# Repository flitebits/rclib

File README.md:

*RCLib*

This is a basic example of bringing up the ATMega 4808/4809 and
enabling the most common hardware. I wrote this so I could use it to
control various features in RC aircraft (telemetry and lights mostly).

I also have some small board designs for the 4808/4809 that I may
include as well.

It has support for:
  * SBus protocol (channel information from radio)
  * S.Port Protocol (only for volts/amps reporting)
  * DSHOT 600 (bit bang) to set motor speed and get telemetry from ESC
  * Analog to Digital conversion (to read battery volts/amps)
  * PWM for controlling 'dumb' leds
  * APA102 (via SPI) & WS2812 (via bit bang)
  * Serial used by several protocols above as well as for debugging
  * Some simple RGB functions for LED control
  * Very minimal debugging log/print support
  * RTC clock

Licensed under the Apache 2.0 license (see the file LICENSE-2.0 for
details).  Please let me know if you decide to use it.

Flite Bits
flitebits@gmail.com

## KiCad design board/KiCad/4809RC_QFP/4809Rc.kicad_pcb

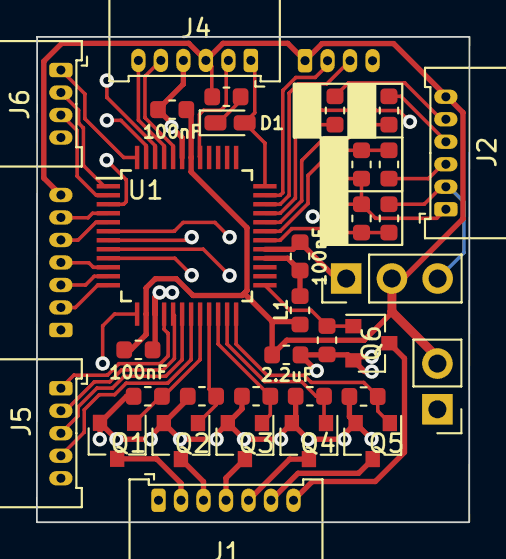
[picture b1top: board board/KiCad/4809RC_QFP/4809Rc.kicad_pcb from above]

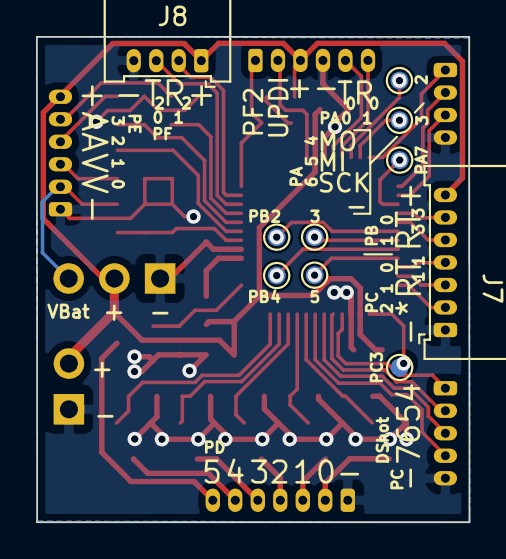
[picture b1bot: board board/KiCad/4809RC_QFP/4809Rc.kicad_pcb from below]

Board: 2 copper layers, 24.0 x 27.0 mm, 47 parts (10 on the bottom side), 50 nets.

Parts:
2.2uF1: 2.2uF; C_0603_1608Metric
100nF1, 100nF2, 100nF3: 100nF; C_0603_1608Metric
C1, C2, C3, C4: 1uF; C_0603_1608Metric
D1: LED; LED_0603_1608Metric_Castellated
J1: Conn_01x09_Male; Molex_PicoBlade_53048-0710_1x07_P1.25mm_Horizontal
J2, J4: Conn_01x06_Male; Molex_PicoBlade_53048-0610_1x06_P1.25mm_Horizontal
J3: Conn_01x03_Female; PinHeader_1x03_P2.54mm_Vertical
J5: Conn_01x05_Male; Molex_PicoBlade_53048-0510_1x05_P1.25mm_Horizontal
J6, J8: Conn_01x04_Male; Molex_PicoBlade_53048-0410_1x04_P1.25mm_Horizontal
J7: Conn_01x07_Male; Molex_PicoBlade_53048-0710_1x07_P1.25mm_Horizontal
J9: Conn_01x02_Male; PinHeader_1x02_P2.54mm_Vertical
L1: L_Core_Ferrite; L_0603_1608Metric
PC3: TestPoint; TestPoint_Pad_D1.0mm
Q1, Q2, Q3, Q4, Q5, Q6: Q_NMOS_GSD; SOT-23
R1, R2, R3, R4, R7, R8: 10K; R_0603_1608Metric
R5, R10: 100K; R_0603_1608Metric
R6, R11: 33K; R_0603_1608Metric
R9, R12, R13: 1K; R_0603_1608Metric
TP1, TP2, TP3, TP4, TP5, TP6, TP7: TestPoint; TestPoint_Pad_D1.0mm
U1: ATmega4809-M; TQFP-48_7x7mm_P0.5mm

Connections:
+5V: 2.2uF1.1, 100nF1.1, 100nF2.1, J2.6, J3.2, J4.3, J7.7, J8.1, J9.2, L1.1, R13.2, U1.14, U1.42
GND: 2.2uF1.2, 100nF1.2, 100nF2.2, 100nF3.2, C1.2, C2.2, C3.2, C4.2, J1.1, J2.1, J3.1, J4.4, J5.5, J6.4, J7.1, J8.4, J9.1, Q1.2, Q2.2, Q3.2, Q4.2, Q5.2, Q6.2, R1.2, R2.2, R3.2, R4.2, R6.2, R7.2, R8.2, R11.2, U1.15, U1.29, U1.43
unnamed: 100nF3.1, L1.2, U1.28
unnamed: C1.1, R5.2, R6.1, U1.31
unnamed: C2.1, R9.2, U1.33
unnamed: C3.1, R10.2, R11.1, U1.30
unnamed: C4.1, R12.2, U1.32
unnamed: D1.1, R13.1
unnamed: D1.2, J4.1, U1.36
unnamed: J1.2, Q1.3
unnamed: J1.3, Q2.3
unnamed: J1.4, Q3.3
unnamed: J1.5, Q4.3
unnamed: J1.6, Q5.3
unnamed: J1.7, Q6.3
unnamed: J2.2, J3.3, R10.1
unnamed: J2.3, R5.1
unnamed: J2.4, R12.1
unnamed: J2.5, R9.1
unnamed: J4.2, U1.41
unnamed: J4.5, U1.44
unnamed: J4.6, U1.45
unnamed: J5.1, U1.16
unnamed: J5.2, U1.17
unnamed: J5.3, U1.18
unnamed: J5.4, U1.19
unnamed: J6.1, U1.48
unnamed: J6.2, U1.1
unnamed: J6.3, U1.2
unnamed: J7.2, U1.12
unnamed: J7.3, U1.11
unnamed: J7.4, U1.10
unnamed: J7.5, U1.5
unnamed: J7.6, U1.4
unnamed: J8.2, U1.35
unnamed: J8.3, U1.34
unnamed: Q1.1, R1.1, U1.20
unnamed: Q2.1, R4.1, U1.21
unnamed: Q3.1, R7.1, U1.22
unnamed: Q4.1, R2.1, U1.23
unnamed: Q5.1, R3.1, U1.24
unnamed: Q6.1, R8.1, U1.25
unnamed: TP1.1, U1.46
unnamed: TP2.1, U1.47
unnamed: TP3.1, U1.6
unnamed: TP4.1, U1.7
unnamed: TP5.1, U1.3
unnamed: TP6.1, U1.8
unnamed: TP7.1, U1.9
unnamed: PC3.1, U1.13

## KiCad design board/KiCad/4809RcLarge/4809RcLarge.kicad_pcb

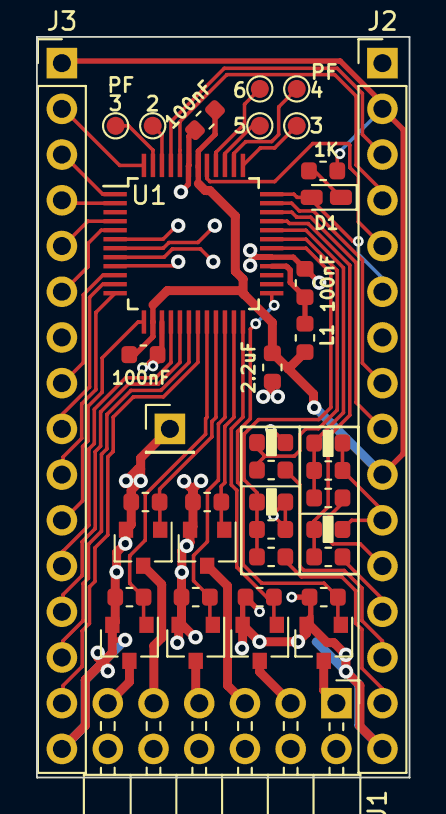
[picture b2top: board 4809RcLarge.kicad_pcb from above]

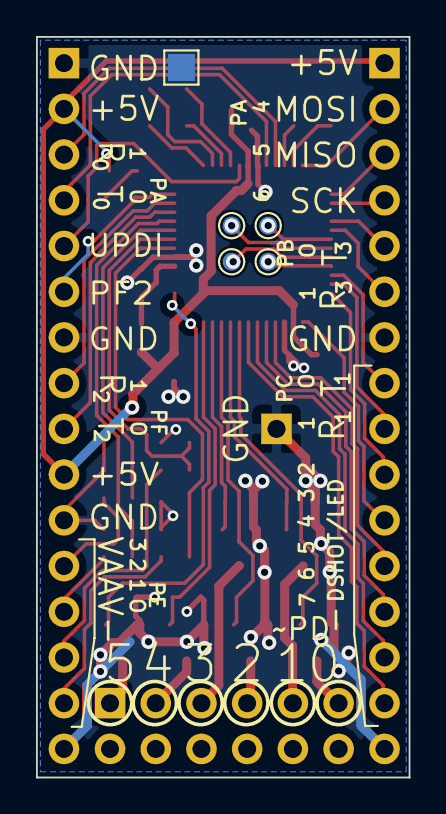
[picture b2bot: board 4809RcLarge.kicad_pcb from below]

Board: 2 copper layers, 20.7 x 41.1 mm, 45 parts (5 on the bottom side), 54 nets.

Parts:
2.2uF, 100nF#2, 100nF#3: 100nF; C_0603_1608Metric
100nF: 2.2uF; C_0603_1608Metric
C1, C2, C3, C4: 1uF; C_0603_1608Metric
D1: LED; LED_0603_1608Metric_Castellated
J1: `; PinHeader_2x06_P2.54mm_Horizontal
J2: Conn_01x06_Male; PinHeader_1x16_P2.54mm_Vertical
J3: Conn_01x16_Male; PinHeader_1x16_P2.54mm_Vertical
J4: Conn_01x01_Male; PinHeader_1x01_P2.54mm_Vertical
L1: L_Core_Ferrite; L_0603_1608Metric
Q1, Q2, Q3, Q4, Q5, Q6: Q_NMOS_GSD; SOT-23
R1, R2, R3, R4, R7, R8: 10K; R_0603_1608Metric
R5, R6: 100K; R_0603_1608Metric
R9, R12, R13: 1K; R_0603_1608Metric
R10, R11: 33K; R_0603_1608Metric
TP1: TestPoint; TestPoint_Pad_1.5x1.5mm
TP2, TP3, TP4, TP5, TP6, TP7, TP8, TP9, TP10, TP11: TestPoint; TestPoint_Pad_D1.0mm
U1: ATmega4809-A; TQFP-48_7x7mm_P0.5mm

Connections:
+5V: 2.2uF.1, 100nF.1, 100nF#3.1, J2.2, J2.10, J3.1, L1.1, R13.2, U1.14, U1.42
GND: 2.2uF.2, 100nF.2, 100nF#2.2, 100nF#3.2, C1.2, C2.2, C3.2, C4.2, J2.1, J2.7, J2.11, J2.16, J3.7, J3.16, J4.1, Q1.2, Q2.2, Q3.2, Q4.2, Q5.2, Q6.2, R1.2, R2.2, R3.2, R4.2, R6.2, R7.2, R8.2, R11.2, TP1.1, U1.15, U1.29, U1.43
unnamed: C1.1, R5.2, R6.1, U1.32
unnamed: C2.1, R9.2, U1.33
unnamed: C3.1, R10.2, R11.1, U1.30
unnamed: C4.1, R12.2, U1.31
unnamed: 100nF#2.1, L1.2, U1.28
unnamed: D1.1, R13.1
unnamed: D1.2, J2.6, U1.36
unnamed: J1.1, Q6.3
unnamed: J1.3, Q3.3
unnamed: J1.5, Q2.3
unnamed: J1.7, Q5.3
unnamed: J1.9, Q4.3
unnamed: J1.11, Q1.3
unnamed: J2.3, U1.45
unnamed: J2.4, U1.44
unnamed: J2.5, U1.41
unnamed: J2.8, U1.35
unnamed: J2.9, U1.34
unnamed: J2.12, R5.1
unnamed: J2.13, R9.1
unnamed: J2.14, R12.1
unnamed: J2.15, R10.1
unnamed: J3.2, U1.48
unnamed: J3.3, U1.1
unnamed: J3.4, U1.2
unnamed: J3.5, U1.4
unnamed: J3.6, U1.5
unnamed: J3.8, U1.10
unnamed: J3.9, U1.11
unnamed: J3.10, U1.12
unnamed: J3.11, U1.13
unnamed: J3.12, U1.16
unnamed: J3.13, U1.17
unnamed: J3.14, U1.18
unnamed: J3.15, U1.19
unnamed: Q1.1, R1.1, U1.20
unnamed: Q2.1, R2.1, U1.23
unnamed: Q3.1, R3.1, U1.24
unnamed: Q4.1, R4.1, U1.21
unnamed: Q5.1, R7.1, U1.22
unnamed: Q6.1, R8.1, U1.25
unnamed: TP2.1, U1.7
unnamed: TP3.1, U1.8
unnamed: TP4.1, U1.9
unnamed: TP5.1, U1.6
unnamed: TP6.1, U1.37
unnamed: TP7.1, U1.38
unnamed: TP8.1, U1.39
unnamed: TP9.1, U1.40
unnamed: TP10.1, U1.46
unnamed: TP11.1, U1.47
VCC: J1.2, J1.4, J1.6, J1.8, J1.10, J1.12

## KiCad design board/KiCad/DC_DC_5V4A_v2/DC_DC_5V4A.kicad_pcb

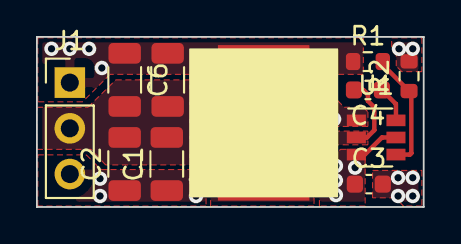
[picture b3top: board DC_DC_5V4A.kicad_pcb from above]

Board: 2 copper layers, 21.5 x 9.4 mm, 11 parts (0 on the bottom side), 6 nets.

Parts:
C1, C2: 10uF; C_1206_3216Metric
C3, C4: 100nF; C_0603_1608Metric
C5, C6: 22uF; C_1206_3216Metric
J1: Conn_01x02; PinHeader_1x03_P2.54mm_Vertical
L1: 3.3uH, 17.7.mOhm, 9.2A; L_Vishay_IHLP-3232
R1: 54.9kOhm; R_0603_1608Metric
R2: 10kOhm; R_0603_1608Metric
U1: TPS565208; SOT-23-6

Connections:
+5V: C5.1, C6.1, J1.1, L1.2, R1.1
+BATT: C1.1, C2.1, C3.1, J1.3, U1.3, U1.5
GND: C1.2, C2.2, C3.2, C5.2, C6.2, J1.2, R2.2, U1.1
unnamed: C4.1, U1.6
unnamed: C4.2, L1.1, U1.2
unnamed: R1.2, R2.1, U1.4

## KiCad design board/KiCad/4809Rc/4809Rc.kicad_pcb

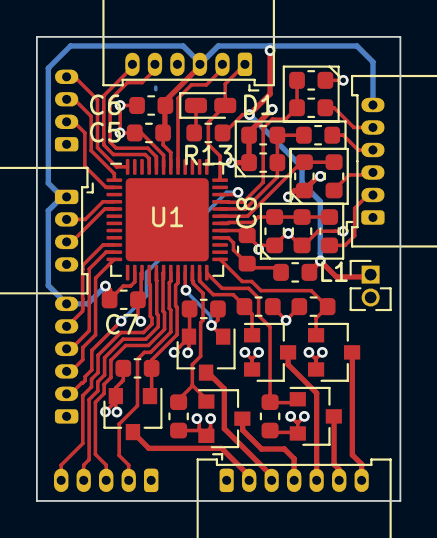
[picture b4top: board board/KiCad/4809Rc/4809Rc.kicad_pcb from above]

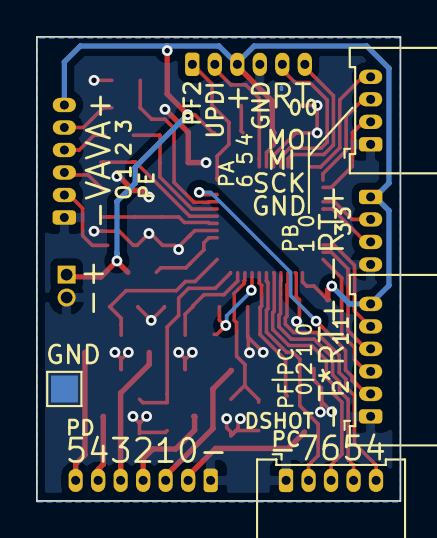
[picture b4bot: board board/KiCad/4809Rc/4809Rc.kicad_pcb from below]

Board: 2 copper layers, 20.2 x 25.8 mm, 39 parts (4 on the bottom side), 41 nets.

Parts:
C1, C2, C3, C4: 1uF; C_0603_1608Metric
C5, C6, C8: 100nF; C_0603_1608Metric
C7: 2.2uF; C_0603_1608Metric
D1: LED; LED_0603_1608Metric_Castellated
GND: TestPoint; TestPoint_Pad_1.5x1.5mm
J1: `; Molex_PicoBlade_53048-0710_1x07_P1.25mm_Horizontal
J2, J4: Conn_01x06_Male; Molex_PicoBlade_53048-0610_1x06_P1.25mm_Horizontal
J3: Conn_01x02; PinHeader_1x02_P1.27mm_Vertical
J5: Conn_01x05_Male; Molex_PicoBlade_53048-0510_1x05_P1.25mm_Horizontal
J6, J8: Conn_01x04_Male; Molex_PicoBlade_53048-0410_1x04_P1.25mm_Horizontal
J7: Conn_01x05_Male; Molex_PicoBlade_53048-0610_1x06_P1.25mm_Horizontal
L1: L_Core_Ferrite; L_0603_1608Metric
Q1, Q2, Q3, Q4, Q5, Q6: Q_NMOS_GSD; SOT-23
R1, R2, R3, R4, R7, R8: 10K; R_0603_1608Metric
R5, R6: 100K; R_0603_1608Metric
R9, R12, R13: 1K; R_0603_1608Metric
R10, R11: 33K; R_0603_1608Metric
U1: ATmega4809-M; UQFN-48-1EP_6x6mm_P0.4mm_EP4.62x4.62mm

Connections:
+5V: C5.1, C6.1, C7.1, J2.6, J3.1, J4.3, J7.6, J8.1, L1.1, R13.2, U1.14, U1.42
GND: C1.2, C2.2, C3.2, C4.2, C5.2, C6.2, C7.2, C8.2, GND.1, J1.1, J2.1, J3.2, J4.4, J5.1, J6.1, J7.1, J8.4, Q1.2, Q2.2, Q3.2, Q4.2, Q5.2, Q6.2, R1.2, R2.2, R3.2, R4.2, R6.2, R7.2, R8.2, R11.2, U1.15, U1.29, U1.43
unnamed: C1.1, R5.2, R6.1, U1.32
unnamed: C2.1, R9.2, U1.33
unnamed: C3.1, R10.2, R11.1, U1.30
unnamed: C4.1, R12.2, U1.31
unnamed: C8.1, L1.2, U1.28
unnamed: D1.1, R13.1
unnamed: D1.2, J4.1, U1.36
unnamed: J1.2, Q1.3
unnamed: J1.3, Q4.3
unnamed: J1.4, Q5.3
unnamed: J1.5, Q2.3
unnamed: J1.6, Q3.3
unnamed: J1.7, Q6.3
unnamed: J2.2, R10.1
unnamed: J2.3, R12.1
unnamed: J2.4, R5.1
unnamed: J2.5, R9.1
unnamed: J4.2, U1.41
unnamed: J4.5, U1.44
unnamed: J4.6, U1.45
unnamed: J5.2, U1.19
unnamed: J5.3, U1.18
unnamed: J5.4, U1.17
unnamed: J5.5, U1.16
unnamed: J6.2, U1.2
unnamed: J6.3, U1.1
unnamed: J6.4, U1.48
unnamed: J7.2, U1.34
unnamed: J7.3, U1.12
unnamed: J7.4, U1.11
unnamed: J7.5, U1.10
unnamed: J8.2, U1.4
unnamed: J8.3, U1.5
unnamed: Q1.1, R1.1, U1.20
unnamed: Q2.1, R2.1, U1.23
unnamed: Q3.1, R3.1, U1.24
unnamed: Q4.1, R4.1, U1.21
unnamed: Q5.1, R7.1, U1.22
unnamed: Q6.1, R8.1, U1.25

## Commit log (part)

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2019-10-03 Initial import to GIT.
2019-10-03 1) Added simple random function. 2) Added Led Fade functions that fade an array of pixels. 2) Added project for FTSportster plane leds.
2019-10-04 Fix compile errors in FTSportster/main.cpp Renamed Rand.cc to Rand.cpp
2019-10-19 1) Split pullup enable from one_wire config (I had trouble with older FrSky receivers doing s.Port with pullup). 2) Added 'App' class to Dbg for user code. 3) Fixed Dbg for Release builds. 4) Switch 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
2019-10-28 1) Added the ability to specify the voltage reference for ADC. 2) Fixed the RGB class order to WS2812, and had the APA102 code pull bytes out in the right order. 3) Added a P38 project that just repo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
2019-11-08 A small amount of cleanup and work on FT Sportster lights. Still need to integrate all the modes.
    Started a test project to try and get ESC Telemetry from a KISS enabled esc.
    So far no luck, I've checked timings for DSHOT 300 with an oscilliscope and they seem good. I kind of suspect I need to do something to prep the ESC. Anyway still a work in progress.
2019-11-11 1) Added a buffered serial option. This uses rx interrupt to read into a rolling buffer (32 bytes). SBus is now using this because driving WS2812 lights takes too much time. 2) Finished first cut of 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
2019-11-15 1) Add more info around interrupt driven Serial reads. It now tracks errors and the fine grained time of the read for time sensitive serial protocols. 2) Migrated SBus protocol to the new Serial inte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
2019-11-16 Added SK6812/WS2812 bitbang implementation. Switched FT Sportster to using that.
2019-12-19 1) Improved Dbg module to have _IF variants. 2) Enhanced Pins.h to make it more useful to work with identified pins. 3) Added needed Atomic block to Serial class. 4) Tweaks to bit bang WS2812 support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
2019-12-20 DShot class is working, and Test code can control motor and get Telemetry.
2020-01-05 1) DShot Implemetation improved a) Uses Asm function for bit banging (better timing) b) Has an ISR based version so you can take time doing other things and still have good timing. 2) Serial now uses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
2020-01-05 Added Apache License to project. Removed some not so interesting code (mostly from me playing around).
2020-02-05 1) Added new project 'Comet'. 2) Added WRGB Gradient lookup functions. 3) Added the ability to mix new random value into Rand seed. 4) Fixed DShot so it will compile in OPT mode (when debug prints ar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
2020-08-17 1) Retuned WS2812 bitbang for PDIV of 1. 2) Created a simple led test project.
2020-10-03 1) First cut of LED program for SkyBoy plane 2) Added Max operator for blending pixels.
2020-11-28 Lots of updates for DSHot related stuff. 1) Split Kiss telemetry out, for fixed wing where there is only one or two ESCs you can configure them with auto telemetry and connect them to different seria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
2020-11-29 1) Added ASM versions of bitbang methods, mostly to avoid compiler changes affecting timing. 2) Fixed argument order for memset (duh!) 3) Updated WingTelemetry for new KissTelemtry interface. 4) Fixe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
2020-12-02 1) Small tweak to KissTelemetry so it resets idx after a successful parse. 2) Fix telemetry requesting in Test/main.cpp 3) cleanup in WingTelem/main.cpp
2021-01-03 1) Added KiCad files for various boards and related items. This includes a very small board (using picoblade connectors) as well as a larger version that uses standard 2.54mm pins. There is also a bu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
    2) Added a bunch of Fixed point math functions, mostly to support my version of Pacifica from WLED.
    3) Fixed a bug in BitBang for WS2812 where it sent bits LSB first instead of MSB first.
    4) Fixed a bug in RtcTime in FastTimeMs where it only returned 16bits.
    5) Leveraged FP math functions in Pixel.ccp
    6) Added new helper functions to RGB pixel classes.
2021-10-17 1) Added some helper methods to PinId (toggle/set/get). 2) Added Get for a Pwm Channel, Added Set multiple interface. 3) Added a slightly better scale8 called bscale8 (has better stability) 4) Added 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
2021-12-19 Finished Large (standard 2.54 pitch pins) board using quad flat pack version of 4809. Added a quad flat pack version of the 'sm' board (not quite as small), the no lead (UQFN) version has had a lot o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
2022-02-21 Added DBG_OFF to disable a debug print that is not desired now but might be again in the future. PWM now has a getter that returns the number of PWM channels available. Fixed a comment error in RtcTi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
2022-02-21 Added lights control module for my FliteTest Master series A10. This has adressable lights in the nacelles and on the tail and pwm lights on the wing tips and in the wing pods. The nacelle lights are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
2022-02-21 Updated Test project to be a simple LED test pattern generator. This is useful on the bench to test led strips and wiring are working. Has animated, and various brightness mode tests. It's still a li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
2022-02-21 Small rework of original twinkle program to handle a new project that involved twinkling leds.
2022-02-21 Huge rewrite of dipper lights control for new build of dual polaris plane. This also has a much better host/client managements system to keep the two controllers in sync between the two hulls. This c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
    Several of the components in this project will probably be split out into utility libraries:
    SynchableChannel which is a really simple packet based protocol used between the host/client that can resync if data is lost/corrupted.
    LedSpan which provides easier access to a span of leds in particular it can reverse indexing, allows code to map the span of leds into a larger
2022-02-24 Added submodes for dipper, also some final tweaks on effects. Whitespace cleanup (untabify and trailing whitespace mostly)
2022-08-07 Provide a standard version of Logify, provide a reusable version of 'VariableSaw'. Make LedSpan a library class.
2022-08-07 New plane BristolSpadport, not complete just some test code for now.
2022-12-22 1) Added support for input Pins.h 2) Wrote a small KeyScan class that can scan row/column keyboards. 3) Started formalizing LedSpanOps which let you fill Led spans with more complex functions (e.g. s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
2023-01-02 Some basic cleanup of RCLib files. Final version of BristolSpadport code. Imported old code for PolarisXL that had been based on Arduino w/ FastLED, updated it for my libs.
2023-01-29 1) Added the ability to set default value when enabling a pwm channel. 2) Added the ability to set the color for an LedSpan from a start index on. 3) Added FT Arrow light control
2023-02-07 1) Added Twi driver, supporting interrupt driven writing only (no read support yet). 2) Added a very basic PCA9685 driver using Twi. This is a 16 channel 12bit PWM chip. This is a nice compliment sin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
2023-07-10 Added Two Wire Interface driver class. Added a Button class for reading state changes of a simple push button. Added logification helpers to Pca9685 driver class (since it's 12 bit). Fixed an off-by-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
2023-08-15 Added PCA 9685 to DaddyO project to control dumb LEDs.
2023-11-18 1) Now supports LEDS with different orders (previously you needed to change member order in RGB/RGBW classes). The 'RGB_LED_ORDER' pre-processor symbol can be defined for your project to the 'numeric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
2024-01-30 Added more modes for Mini7/main.cpp Added LogoPlaque project.
2024-02-21 Mostly updates to LogoPlaque/main.cpp.
2024-09-27 Final version of Logo Plaque code.
2024-09-27 1) Dbg added new topic 'Dbg' 2) Small improvements to Pca9685::Apparent2Pwm 3) Serial added 'DumpReadBuffer' for debugging serial commands. 4) Small tweaks to WS2812 timing (shouldn't really matter).
2024-09-27 Added DbgCmds and VarCmds which enable triggering registered commands and setting variables via the Dbg Serial port.
2024-09-27 Updated projects. Test got DbgCmd support dipper is updated for new build. LedArmature is a quick project for driving a small number of leds. P51D is code for LEDS in 3dLab print 55" P51D
2024-11-28 Added Bucknell Bison, and BungieProp projects
2024-12-21 Adding Code for Flying Porcupine plaque. Also final updates to Bucknell Bison plaque
2025-04-12 Updated P51D for new led strip lengths. Fixed dipper so it works with the new build.
2025-07-11 Adding an LED Bucknell Bison Logo driver Adding LED drivers for my Eclipson B XL
